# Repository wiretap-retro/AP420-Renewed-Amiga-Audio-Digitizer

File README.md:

# AP420 Renewed Amiga Audio Digitizer
A remake of the Phoenix Microtechnologies AP420 with mono input and TRS microphone jack.

## Information
The schematic is per the PDF manual in the respository from the Phoenix Microtechnologies AP420. I added a second RCA jack so you can hook up stereo sound and it will be combined to a mono input. There's also an updated microphone jack that supports TRS 3.5mm and goes to a mono input. The selector switch on the board allows you to select between the RCA input and the microphone input. VR1 is a gain control knob for adjusting the strength of the audio signal.
\
\
The AP420 manual also goes into some detail in the notes section for performing component changes to allow for different audio sample rates at the expense of audio quality.
\
\
This device hooks up to the parallel port of of an Amiga 500, 600, 1000 (with adapter), 1200, 2000, 3000, and 4000. It does not require any external power.

## Misc
Not built and tested yet. Feel free to evaluate the circuit and provide any feedback.

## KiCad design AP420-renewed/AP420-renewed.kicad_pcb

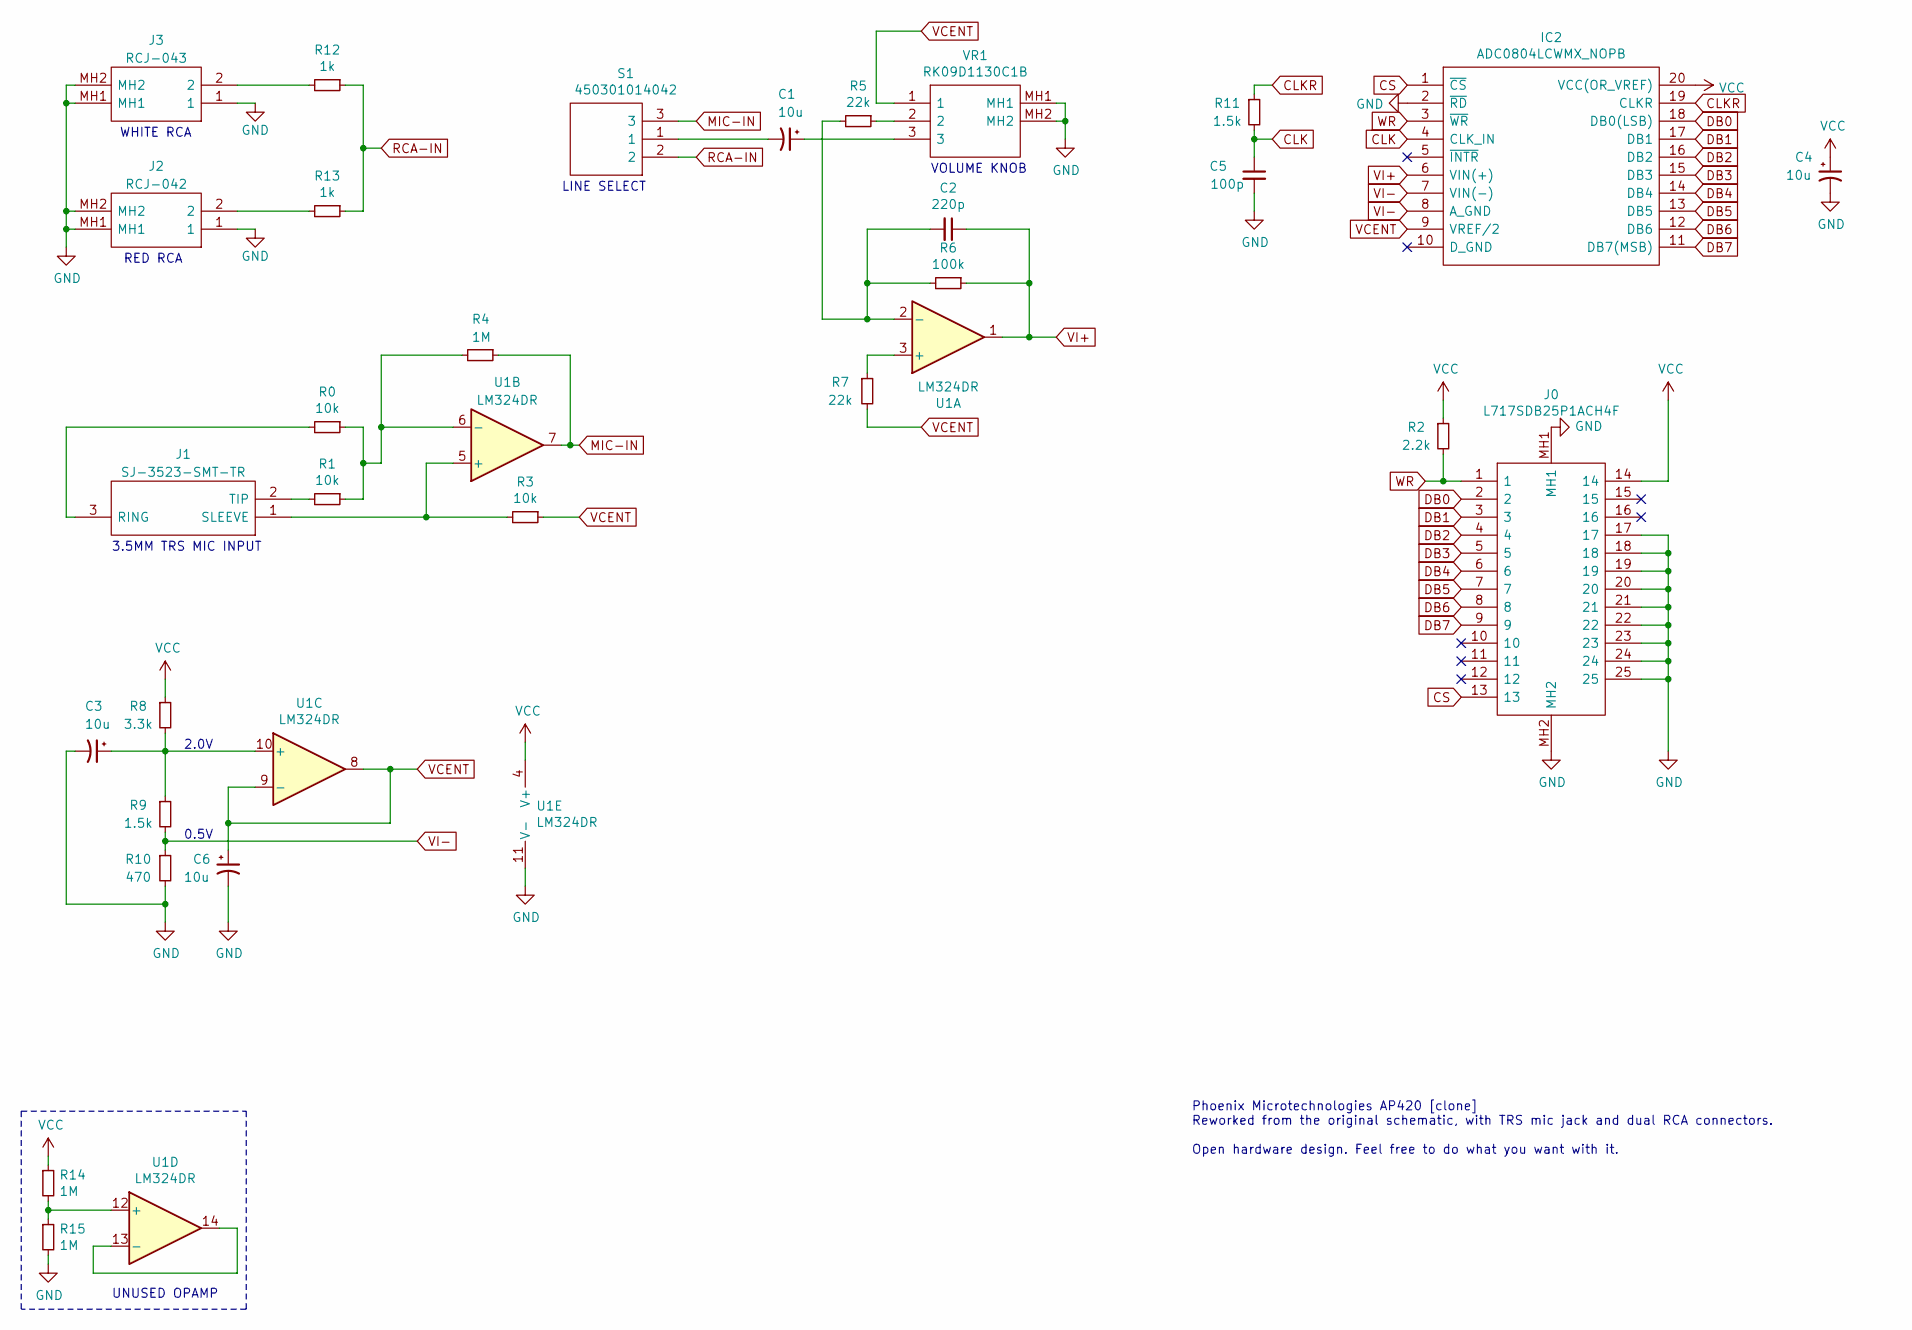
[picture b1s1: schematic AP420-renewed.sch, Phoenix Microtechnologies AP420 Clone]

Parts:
C1, C3, C4, C6: 10u; CP_Elec_4x5.8
C2: 220p; C_0805_2012Metric_Pad1.15x1.40mm_HandSolder
C5: 100p; C_0805_2012Metric_Pad1.15x1.40mm_HandSolder
IC2: ADC0804LCWMX_NOPB; SOIC127P1030X265-20N; Mouser Part Number 926-ADC0804LCWMXNOPB
J0: L717SDB25P1ACH4F; Mouser Part Number 523-L717SDB25P1ACH4F
J1: SJ-3523-SMT-TR; SJ3523SMTTR; Mouser Part Number 490-SJ-3523-SMT-TR
J2: RCJ-042; RCJ042; Mouser Part Number 490-RCJ-042
J3: RCJ-043; RCJ043; Mouser Part Number 490-RCJ-043
R0, R1, R3: 10k; R_0805_2012Metric_Pad1.15x1.40mm_HandSolder
R2: 2.2k; R_0805_2012Metric_Pad1.15x1.40mm_HandSolder
R4, R14, R15: 1M; R_0805_2012Metric_Pad1.15x1.40mm_HandSolder
R5, R7: 22k; R_0805_2012Metric_Pad1.15x1.40mm_HandSolder
R6: 100k; R_0805_2012Metric_Pad1.15x1.40mm_HandSolder
R8: 3.3k; R_0805_2012Metric_Pad1.15x1.40mm_HandSolder
R9, R11: 1.5k; R_0805_2012Metric_Pad1.15x1.40mm_HandSolder
R10: 470; R_0805_2012Metric_Pad1.15x1.40mm_HandSolder
R12, R13: 1k; R_0805_2012Metric_Pad1.15x1.40mm_HandSolder
S1: 450301014042; Mouser Part Number 710-450301014042
U1: LM324DR; SOIC127P600X175-14N
VR1: RK09D1130C1B; Mouser Part Number 688-RK09D1130C1B

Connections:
CLK: C5.1, IC2.4 (CLK_IN), R11.2
CLKR: IC2.19 (CLKR), R11.1
CS: IC2.1 (~CS), J0.13
DB0: IC2.18 (DB0(LSB)), J0.2
DB1: IC2.17 (DB1), J0.3
DB2: IC2.16 (DB2), J0.4
DB3: IC2.15 (DB3), J0.5
DB4: IC2.14 (DB4), J0.6
DB5: IC2.13 (DB5), J0.7
DB6: IC2.12 (DB6), J0.8
DB7: IC2.11 (DB7(MSB)), J0.9
GND: C3.2, C4.2, C5.2, C6.2, IC2.2 (~RD), J0.17, J0.18, J0.19, J0.20, J0.21, J0.22, J0.23, J0.24, J0.25, J0.MH1, J0.MH2, J2.1, J2.MH1, J2.MH2, J3.1, J3.MH1, J3.MH2, R10.2, R15.2, U1.11 (V-), VR1.MH1, VR1.MH2
MIC-IN: R4.1, S1.3, U1.7
unnamed: C1.1, VR1.3
unnamed: C1.2, S1.1
unnamed: C2.2, R5.2, R6.2, U1.2 (-)
unnamed: C3.1, R8.2, R9.1, U1.10 (+)
unnamed: J1.1 (SLEEVE), R3.2, U1.5 (+)
unnamed: J1.2 (TIP), R1.2
unnamed: J1.3 (RING), R0.2
unnamed: J2.2, R13.2
unnamed: J3.2, R12.2
unnamed: R0.1, R1.1, R4.2, U1.6 (-)
unnamed: R5.1, VR1.2
unnamed: R7.1, U1.3 (+)
unnamed: R14.2, R15.1, U1.12 (+)
unnamed: U1.13 (-), U1.14
RCA-IN: R12.1, R13.1, S1.2
VCC: C4.1, IC2.20 (VCC(OR_VREF)), J0.14, R2.1, R8.1, R14.1, U1.4 (V+)
VCENT: C6.1, IC2.9 (VREF/2), R3.1, R7.2, U1.8, U1.9 (-), VR1.1
VI+: C2.1, IC2.6 (VIN(+)), R6.1, U1.1
VI-: IC2.7 (VIN(-)), IC2.8 (A_GND), R9.2, R10.1
WR: IC2.3 (~WR), J0.1, R2.2

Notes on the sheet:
UNUSED OPAMP
3.5MM TRS MIC INPUT
WHITE RCA
RED RCA
LINE SELECT
VOLUME KNOB
0.5V
2.0V
Phoenix Microtechnologies AP420 [clone] Reworked from the original schematic, with TRS mic jack and dual RCA connectors. Open hardware design. Feel free to do what you want with it.

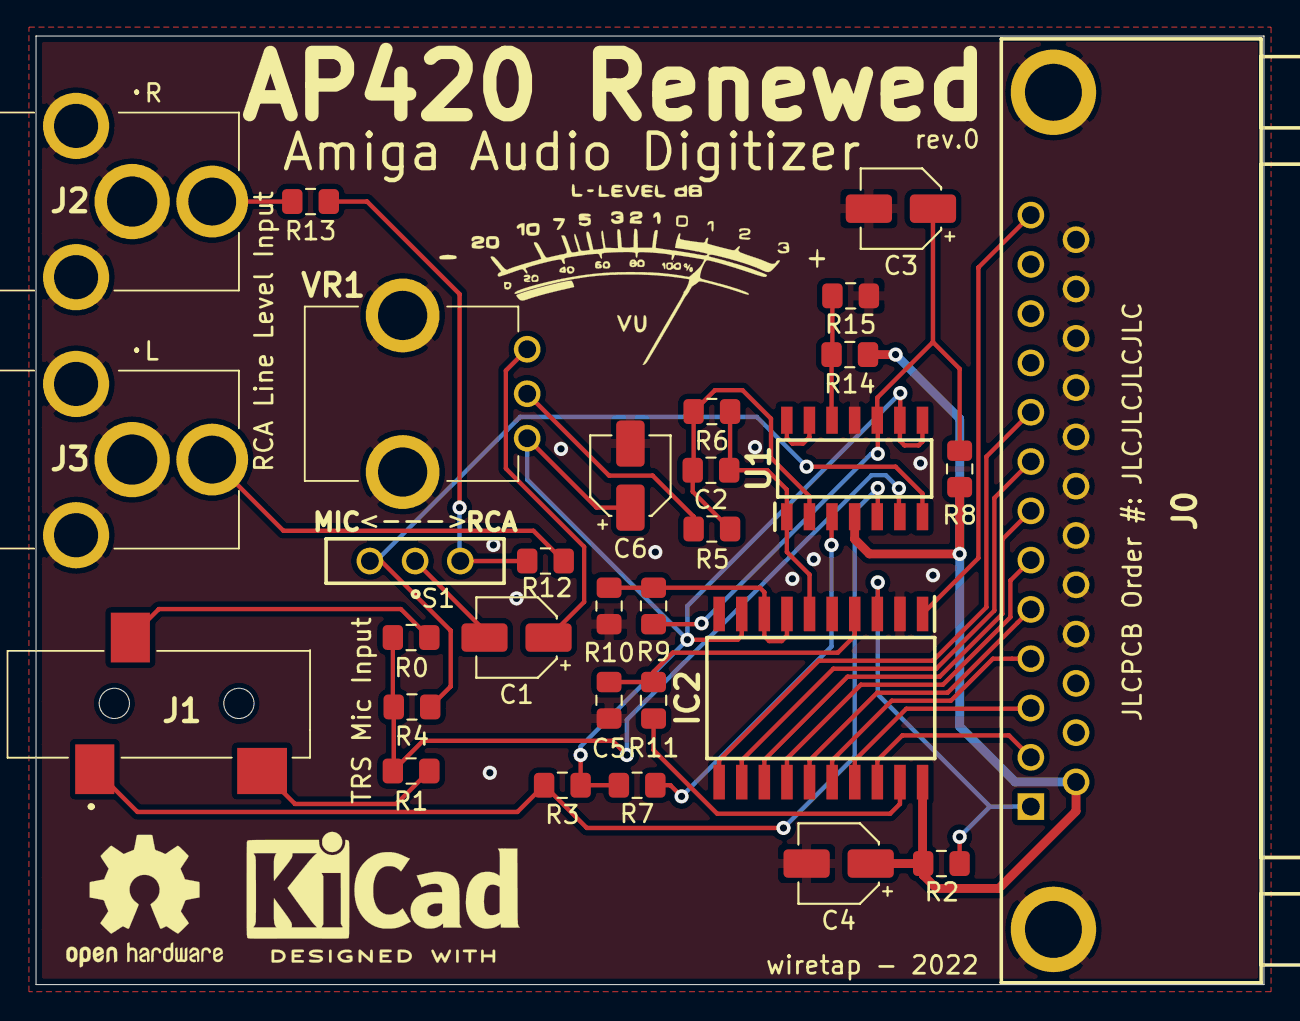
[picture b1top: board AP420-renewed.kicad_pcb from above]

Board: 2 copper layers, 69.0 x 53.3 mm, 30 parts (0 on the bottom side), 33 nets.

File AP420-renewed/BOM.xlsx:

Reference | Value | Footprint | Description | Manufacturer_Name | Manufacturer_Part_Number | Mouser Part Number
C1 | 10u | Capacitor_SMD:CP_Elec_4x5.8
C2 | 220p | Capacitor_SMD:C_0805_2012Metric_Pad1.15x1.40mm_HandSolder
C3 | 10u | Capacitor_SMD:CP_Elec_4x5.8
C4 | 10u | Capacitor_SMD:CP_Elec_4x5.8
C5 | 100p | Capacitor_SMD:C_0805_2012Metric_Pad1.15x1.40mm_HandSolder
C6 | 10u | Capacitor_SMD:CP_Elec_4x5.8
IC2 | ADC0804LCWMX_NOPB | SOIC127P1030X265-20N | 8-Bit, 1-Ch P Compatible A/D Converters with 1 LSB INL | Texas Instruments | ADC0804LCWMX/NOPB | 926-ADC0804LCWMXNOPB
J0 | L717SDB25P1ACH4F | L717SDB25P1ACH4F | Dsub, Stamped Signal 3A, Right Angle PCB Through Hole, FP=10.40mm (0.409in), Ro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 | Amphenol | L717SDB25P1ACH4F | 523-L717SDB25P1ACH4F
J1 | SJ-3523-SMT-TR | SJ3523SMTTR | Phone Connectors Audio Jacks | CUI Inc. | SJ-3523-SMT-TR | 490-SJ-3523-SMT-TR
J2 | RCJ-042 | RCJ042 | RCA Phono Connectors RCA Connectors | CUI Inc. | RCJ-042 | 490-RCJ-042
J3 | RCJ-043 | RCJ043 | RCA Phono Connectors RCA Connectors | CUI Inc. | RCJ-042 | 490-RCJ-043
R0 | 10k | Resistor_SMD:R_0805_2012Metric_Pad1.15x1.40mm_HandSolder
R1 | 10k | Resistor_SMD:R_0805_2012Metric_Pad1.15x1.40mm_HandSolder
R10 | 470 | Resistor_SMD:R_0805_2012Metric_Pad1.15x1.40mm_HandSolder
R11 | 1.5k | Resistor_SMD:R_0805_2012Metric_Pad1.15x1.40mm_HandSolder
R12 | 1k | Resistor_SMD:R_0805_2012Metric_Pad1.15x1.40mm_HandSolder
R13 | 1k | Resistor_SMD:R_0805_2012Metric_Pad1.15x1.40mm_HandSolder
R14 | 1M | Resistor_SMD:R_0805_2012Metric_Pad1.15x1.40mm_HandSolder
R15 | 1M | Resistor_SMD:R_0805_2012Metric_Pad1.15x1.40mm_HandSolder
R2 | 2.2k | Resistor_SMD:R_0805_2012Metric_Pad1.15x1.40mm_HandSolder
R3 | 10k | Resistor_SMD:R_0805_2012Metric_Pad1.15x1.40mm_HandSolder
R4 | 1M | Resistor_SMD:R_0805_2012Metric_Pad1.15x1.40mm_HandSolder
R5 | 22k | Resistor_SMD:R_0805_2012Metric_Pad1.15x1.40mm_HandSolder
R6 | 100k | Resistor_SMD:R_0805_2012Metric_Pad1.15x1.40mm_HandSolder
R7 | 22k | Resistor_SMD:R_0805_2012Metric_Pad1.15x1.40mm_HandSolder
R8 | 3.3k | Resistor_SMD:R_0805_2012Metric_Pad1.15x1.40mm_HandSolder
R9 | 1.5k | Resistor_SMD:R_0805_2012Metric_Pad1.15x1.40mm_HandSolder
S1 | 450301014042 | 450301014042 | Mini Slide Switch 10x2.5mm SPDT on / on Through Hole Slide Switch SPDT On-On 10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 | Wurth Elektronik | 450301014042 | 710-450301014042
U1 | LM324DR | SamacSys_Parts:SOIC127P600X175-14N | Operational Amplifiers - Op Amps Quad GP Op Amp | Texas Instruments | LM324DR | 595-LM324DR
VR1 | RK09D1130C1B | RK09D1130C1B | Audio single pot. 10K Vertical 20mm,1B Alps Potentiometer RK09D Series with a 6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 | ALPS Electric | RK09D1130C1B | 688-RK09D1130C1B
